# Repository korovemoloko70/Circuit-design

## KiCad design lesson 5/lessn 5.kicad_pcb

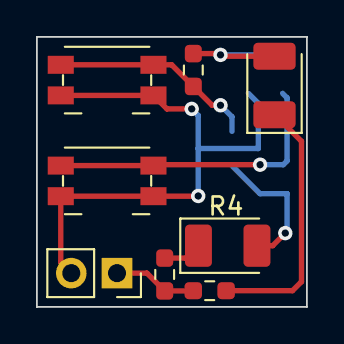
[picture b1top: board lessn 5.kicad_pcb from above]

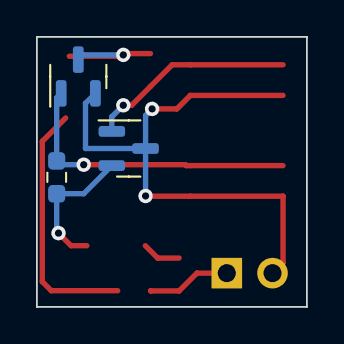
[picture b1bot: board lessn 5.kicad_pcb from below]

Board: 2 copper layers, 15.0 x 15.0 mm, 11 parts (3 on the bottom side), 8 nets.

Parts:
C1: C2; CP_EIA-3528-21_Kemet-B_Pad1.50x2.35mm_HandSolder
C2: C1; CP_EIA-3528-21_Kemet-B_Pad1.50x2.35mm_HandSolder
J1: Power; PinSocket_1x02_P2.54mm_Vertical
Q1, Q2: Q_NPN_BEC; SOT-23
R1, R2, R3, R4: R; R_0603_1608Metric_Pad0.98x0.95mm_HandSolder
SW1, SW2: Button; Panasonic_EVQPUK_EVQPUB

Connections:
+5V: J1.1, R1.2, R4.1
GND: J1.2, Q1.3 (C), Q2.2 (E), SW1.1, SW2.1
unnamed: C1.1, R1.1
unnamed: C1.2, Q1.2 (E), R2.1
unnamed: C2.1, R4.2
unnamed: C2.2, Q2.3 (C), R3.1
unnamed: Q1.1 (B), R3.2, SW1.2
unnamed: Q2.1 (B), R2.2, SW2.2
